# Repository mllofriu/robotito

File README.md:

# robotito
Robotito software and designs

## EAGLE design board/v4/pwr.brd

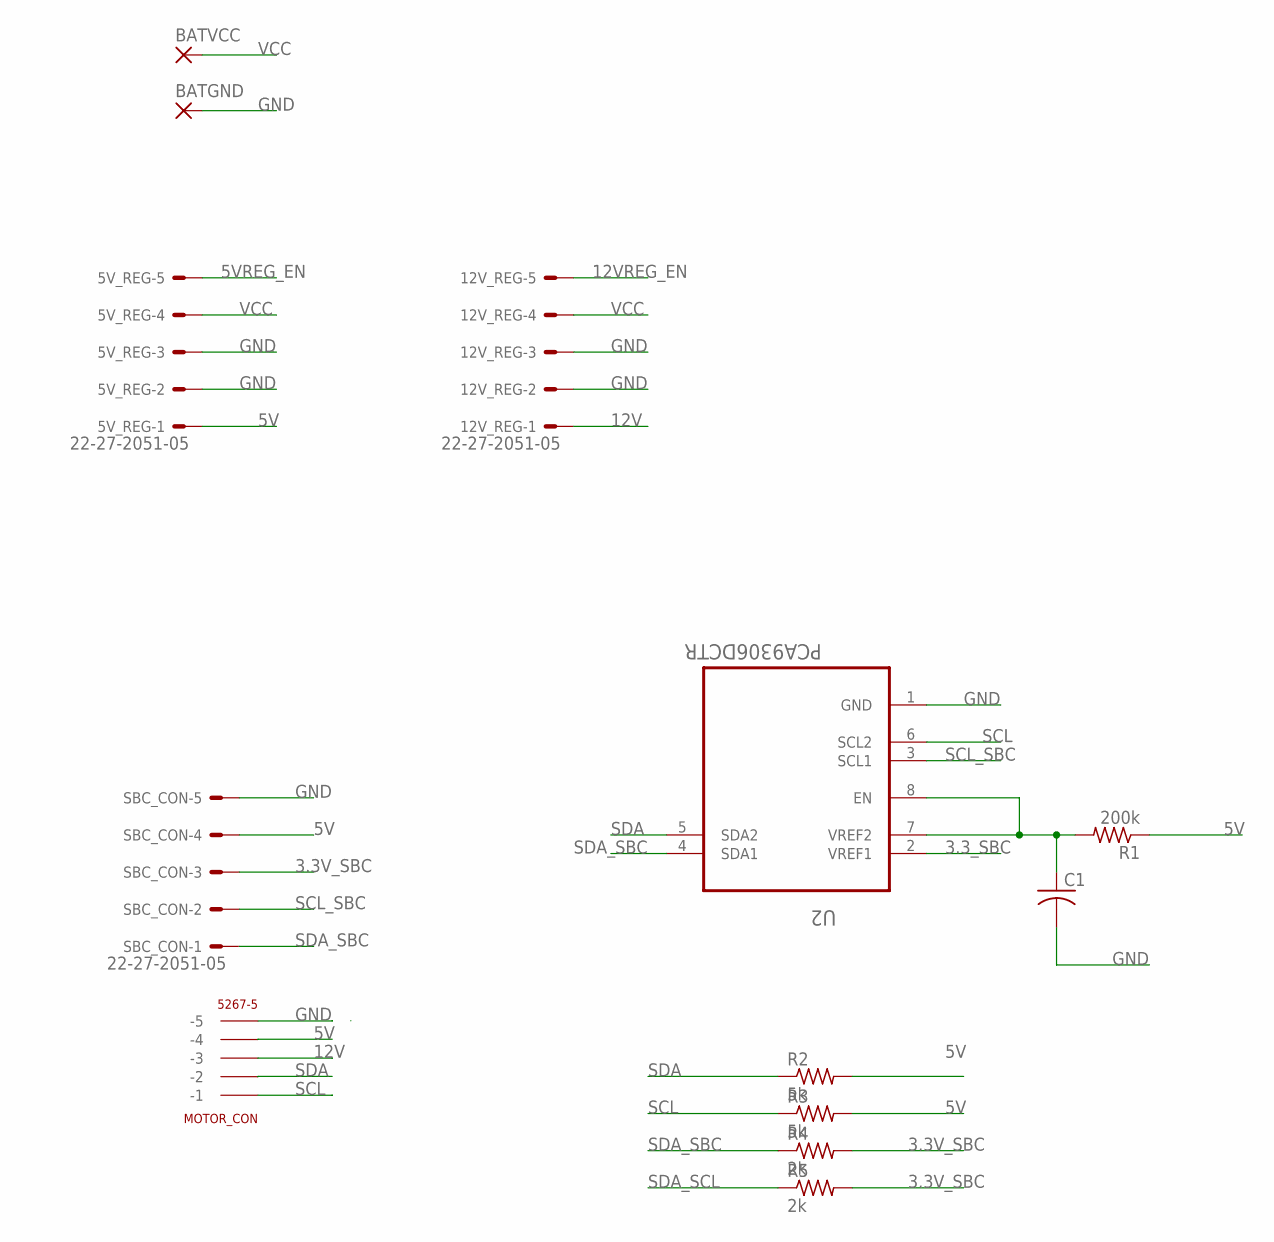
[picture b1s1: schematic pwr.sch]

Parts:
5V_REG, 12V_REG: 22-27-2051-05; 6410-05
BATGND: SMD5; SMD2,54-5,08
BATVCC: SMD5; SMD2,54-5,08
C1: C-USC1210; C1210
MOTOR_CON: 5267-5
R1: 200k; R1210
R2, R3: 5k; R1210
R4, R5: 2k; R1210
SBC_CON: 22-27-2051-05; 6410-05
U2: PCA9306DCTR; SOP65P400X130-8N

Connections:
3.3V_SBC: R4.2, R5.2, SBC_CON.3
3.3_SBC: U2.2 (VREF1)
5V: 5V_REG.1, MOTOR_CON.P$4 (-4), R1.1, R2.2, R3.2, SBC_CON.4
5VREG_EN: 5V_REG.5
12V: 12V_REG.1, MOTOR_CON.P$3 (-3)
12VREG_EN: 12V_REG.5
GND: 5V_REG.2, 5V_REG.3, 12V_REG.2, 12V_REG.3, BATGND.1, C1.2, MOTOR_CON.P$5 (-5), SBC_CON.5, U2.1 (GND)
unnamed: C1.1, R1.2, U2.7 (VREF2), U2.8 (EN)
SCL: MOTOR_CON.P$1 (-1), R3.1, U2.6 (SCL2)
SCL_SBC: SBC_CON.2, U2.3 (SCL1)
SDA: MOTOR_CON.P$2 (-2), R2.1, U2.5 (SDA2)
SDA_SBC: R4.1, SBC_CON.1, U2.4 (SDA1)
SDA_SCL: R5.1
VCC: 5V_REG.4, 12V_REG.4, BATVCC.1

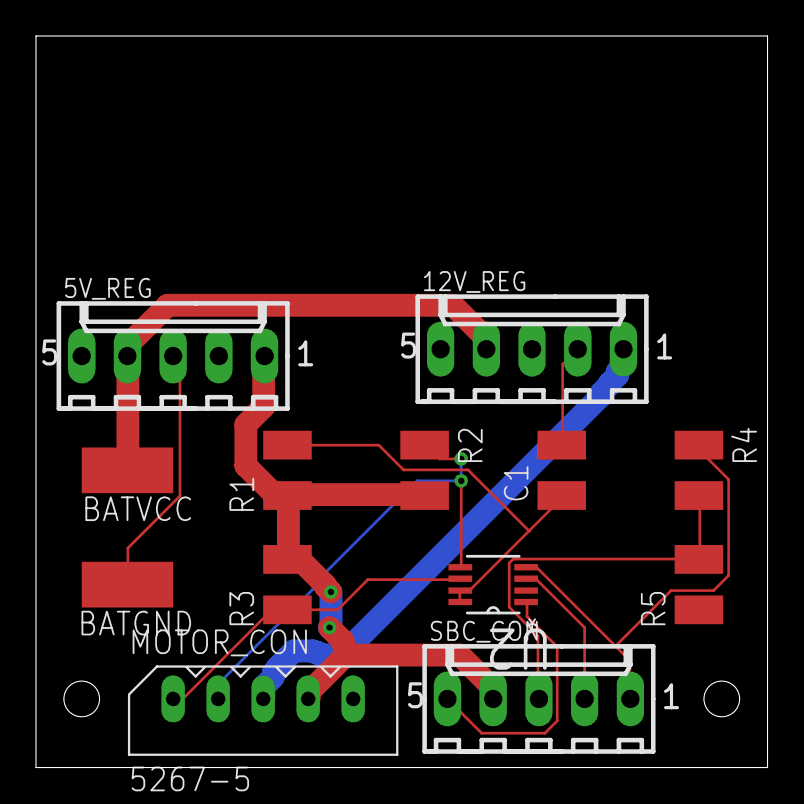
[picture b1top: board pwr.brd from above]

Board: 2 copper layers, 40.6 x 40.6 mm, 13 parts (0 on the bottom side), 10 nets.

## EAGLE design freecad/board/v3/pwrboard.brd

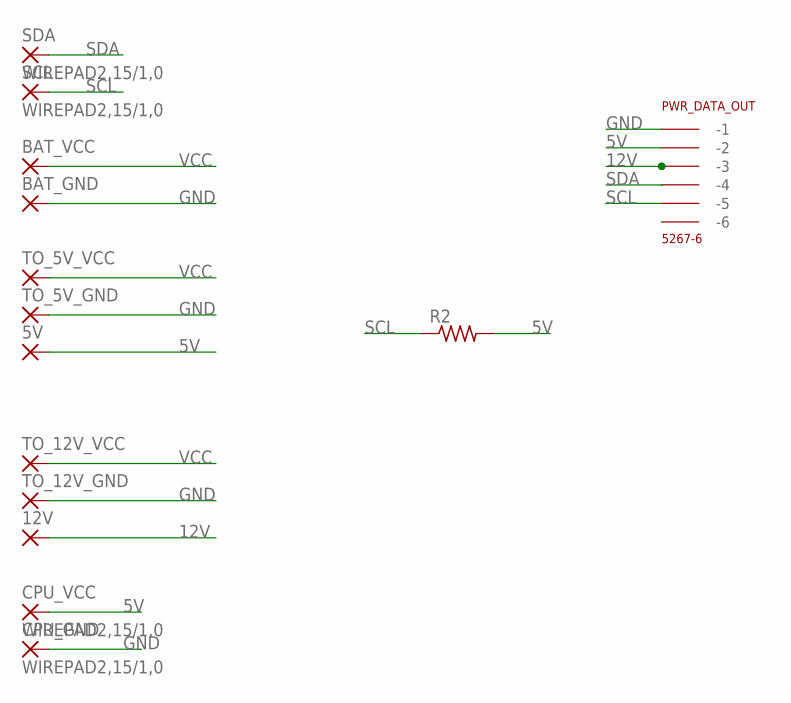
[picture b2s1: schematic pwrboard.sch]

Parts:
5V, 12V: SMD5; SMD2,54-5,08
BAT_GND: SMD5; SMD2,54-5,08
BAT_VCC: SMD5; SMD2,54-5,08
CPU_GND: WIREPAD2,15/1,0; 2,15/1,0
CPU_VCC: WIREPAD2,15/1,0; 2,15/1,0
PWR_DATA_OUT: 5267-6
R2: R-US_R1210; R1210
SCL: WIREPAD2,15/1,0; 2,15/1,0
SDA: WIREPAD2,15/1,0; 2,15/1,0
TO_5V_GND, TO_5V_VCC, TO_12V_GND, TO_12V_VCC: SMD5; SMD2,54-5,08

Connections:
5V: 5V.1, CPU_VCC.1, PWR_DATA_OUT.P$2 (-2), R2.2
12V: 12V.1, PWR_DATA_OUT.P$3 (-3)
GND: BAT_GND.1, CPU_GND.1, PWR_DATA_OUT.P$1 (-1), TO_5V_GND.1, TO_12V_GND.1
SCL: PWR_DATA_OUT.P$5 (-5), R2.1, SCL.1
SDA: PWR_DATA_OUT.P$4 (-4), SDA.1
VCC: BAT_VCC.1, TO_5V_VCC.1, TO_12V_VCC.1

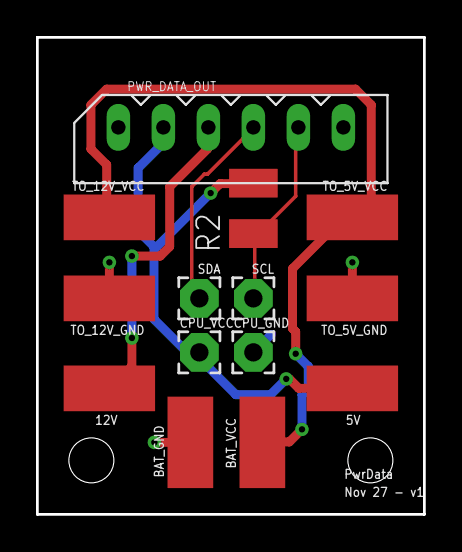
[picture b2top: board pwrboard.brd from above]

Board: 2 copper layers, 21.5 x 26.5 mm, 14 parts (0 on the bottom side), 6 nets.

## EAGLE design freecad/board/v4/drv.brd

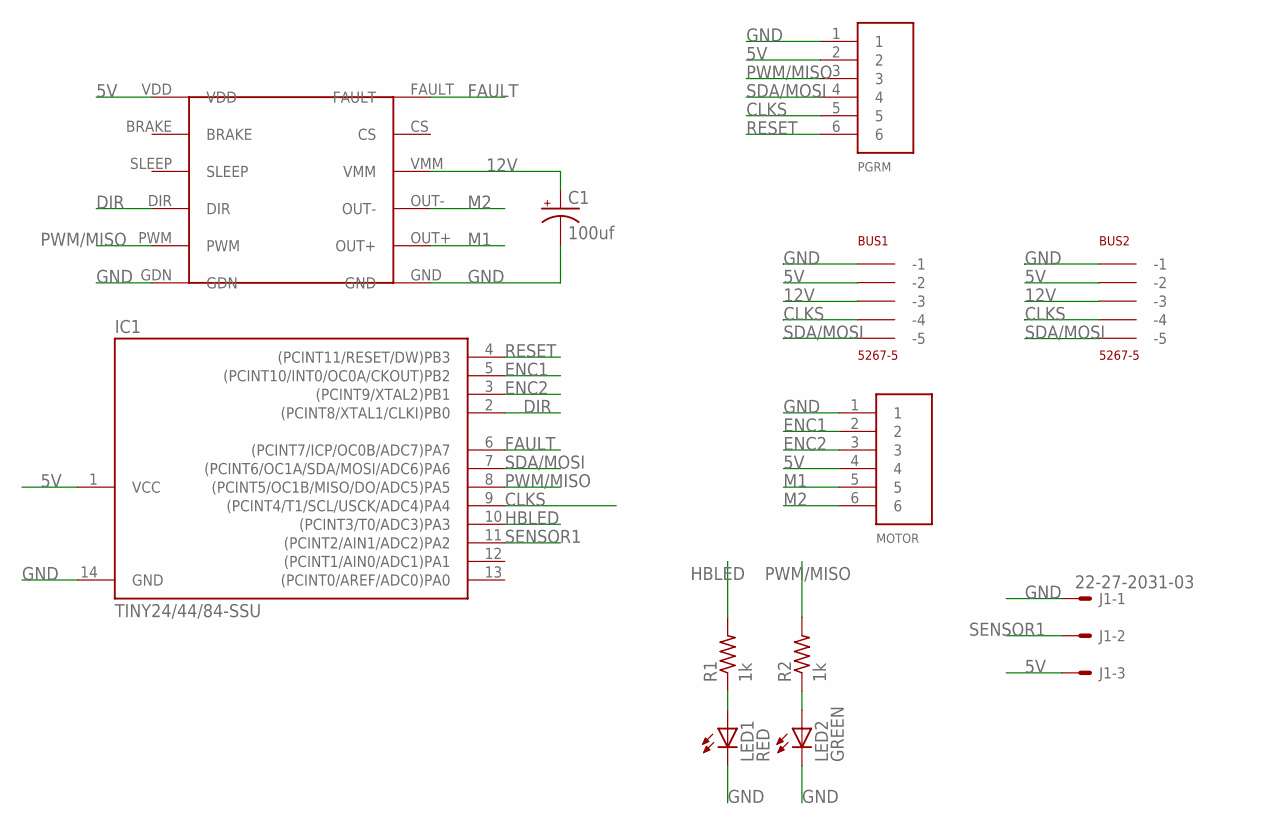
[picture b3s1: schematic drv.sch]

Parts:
BUS1, BUS2: 5267-5
C1: 100uf; E5-10,5
IC1: TINY24/44/84-SSU; SOIC14
J1: 22-27-2031-03; 6410-03
LED1: RED; 1206
LED2: GREEN; 1206
MOTOR: 6PIN; B6B-PH-K-S
PGRM: 6PIN; B6B-PH-K-S
R1, R2: 1k; M1206
U$1: DRV8801BR

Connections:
5V: BUS1.P$2 (-2), BUS2.P$2 (-2), IC1.1 (VCC), J1.3, MOTOR.4, PGRM.2, U$1.VDD
12V: BUS1.P$3 (-3), BUS2.P$3 (-3), C1.+, U$1.VMM
CLKS: BUS1.P$4 (-4), BUS2.P$4 (-4), IC1.9 ((PCINT4/T1/SCL/USCK/ADC4)PA4), PGRM.5
DIR: IC1.2 ((PCINT8/XTAL1/CLKI)PB0), U$1.DIR
ENC1: IC1.5 ((PCINT10/INT0/OC0A/CKOUT)PB2), MOTOR.2
ENC2: IC1.3 ((PCINT9/XTAL2)PB1), MOTOR.3
FAULT: IC1.6 ((PCINT7/ICP/OC0B/ADC7)PA7), U$1.FAULT
GND: BUS1.P$1 (-1), BUS2.P$1 (-1), C1.-, IC1.14 (GND), J1.1, LED1.C, LED2.C, MOTOR.1, PGRM.1, U$1.GDN, U$1.GND
HBLED: IC1.10 ((PCINT3/T0/ADC3)PA3), R1.2
M1: MOTOR.5, U$1.OUT+
M2: MOTOR.6, U$1.OUT-
unnamed: LED1.A, R1.1
unnamed: LED2.A, R2.1
PWM/MISO: IC1.8 ((PCINT5/OC1B/MISO/DO/ADC5)PA5), PGRM.3, R2.2, U$1.PWM
RESET: IC1.4 ((PCINT11/RESET/DW)PB3), PGRM.6
SDA/MOSI: BUS1.P$5 (-5), BUS2.P$5 (-5), IC1.7 ((PCINT6/OC1A/SDA/MOSI/ADC6)PA6), PGRM.4
SENSOR1: IC1.11 ((PCINT2/AIN1/ADC2)PA2), J1.2

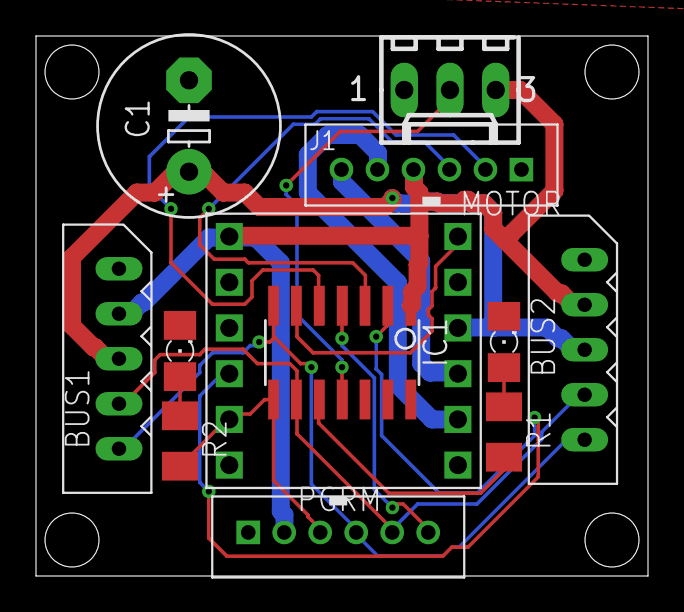
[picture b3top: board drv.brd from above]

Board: 2 copper layers, 34.0 x 30.0 mm, 12 parts (0 on the bottom side), 17 nets.

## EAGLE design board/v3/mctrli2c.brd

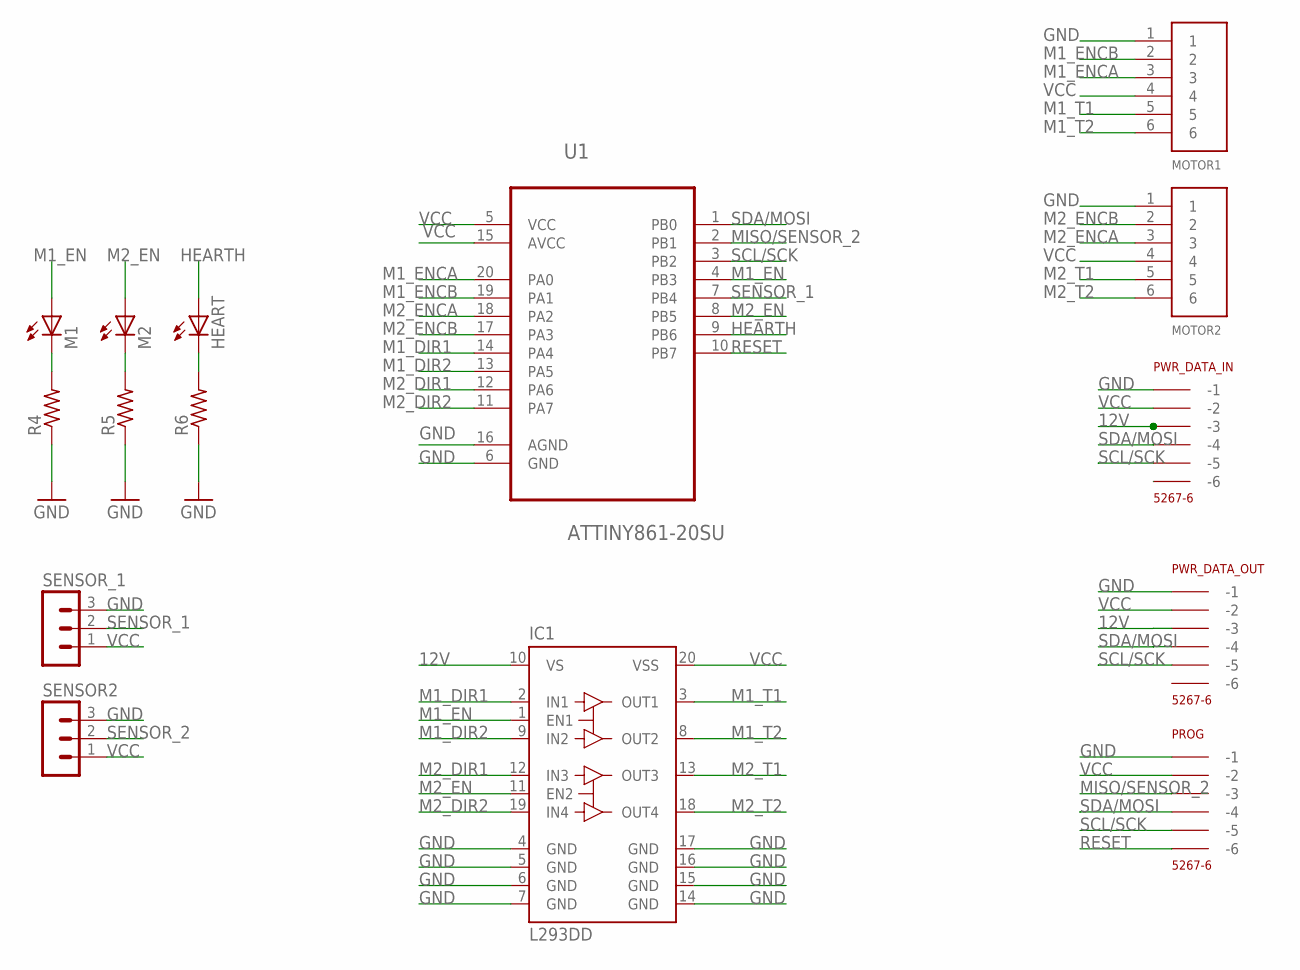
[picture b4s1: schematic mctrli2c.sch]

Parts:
HEART: LEDSML1206; SML1206
IC1: L293DD; SO20
M1, M2: LEDSML1206; SML1206
MOTOR1, MOTOR2: 6PIN; B6B-PH-K-S
PROG: 5267-6
PWR_DATA_IN: 5267-6
PWR_DATA_OUT: 5267-6
R4, R5, R6: R-US_R1210; R1210
SENSOR2: MA03-1
SENSOR_1: MA03-1
U1: ATTINY861-20SU; SOIC127P1032X265-20N

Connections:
12V: IC1.10 (VS), PWR_DATA_IN.P$3 (-3), PWR_DATA_OUT.P$3 (-3)
GND: IC1.4 (GND), IC1.5 (GND), IC1.6 (GND), IC1.7 (GND), IC1.14 (GND), IC1.15 (GND), IC1.16 (GND), IC1.17 (GND), MOTOR1.1, MOTOR2.1, PROG.P$1 (-1), PWR_DATA_IN.P$1 (-1), PWR_DATA_OUT.P$1 (-1), R4.1, R5.1, R6.1, SENSOR2.3, SENSOR_1.3, U1.6 (GND), U1.16 (AGND)
HEARTH: HEART.A, U1.9 (PB6)
M1_DIR1: IC1.2 (IN1), U1.14 (PA4)
M1_DIR2: IC1.9 (IN2), U1.13 (PA5)
M1_EN: IC1.1 (EN1), M1.A, U1.4 (PB3)
M1_ENCA: MOTOR1.3, U1.20 (PA0)
M1_ENCB: MOTOR1.2, U1.19 (PA1)
M1_T1: IC1.3 (OUT1), MOTOR1.5
M1_T2: IC1.8 (OUT2), MOTOR1.6
M2_DIR1: IC1.12 (IN3), U1.12 (PA6)
M2_DIR2: IC1.19 (IN4), U1.11 (PA7)
M2_EN: IC1.11 (EN2), M2.A, U1.8 (PB5)
M2_ENCA: MOTOR2.3, U1.18 (PA2)
M2_ENCB: MOTOR2.2, U1.17 (PA3)
M2_T1: IC1.13 (OUT3), MOTOR2.5
M2_T2: IC1.18 (OUT4), MOTOR2.6
MISO/SENSOR_2: PROG.P$3 (-3), U1.2 (PB1)
unnamed: M1.C, R4.2
unnamed: M2.C, R5.2
unnamed: HEART.C, R6.2
RESET: PROG.P$6 (-6), U1.10 (PB7)
SCL/SCK: PROG.P$5 (-5), PWR_DATA_IN.P$5 (-5), PWR_DATA_OUT.P$5 (-5), U1.3 (PB2)
SDA/MOSI: PROG.P$4 (-4), PWR_DATA_IN.P$4 (-4), PWR_DATA_OUT.P$4 (-4), U1.1 (PB0)
SENSOR_1: SENSOR_1.2, U1.7 (PB4)
SENSOR_2: SENSOR2.2
VCC: IC1.20 (VSS), MOTOR1.4, MOTOR2.4, PROG.P$2 (-2), PWR_DATA_IN.P$2 (-2), PWR_DATA_OUT.P$2 (-2), SENSOR2.1, SENSOR_1.1, U1.5 (VCC), U1.15 (AVCC)

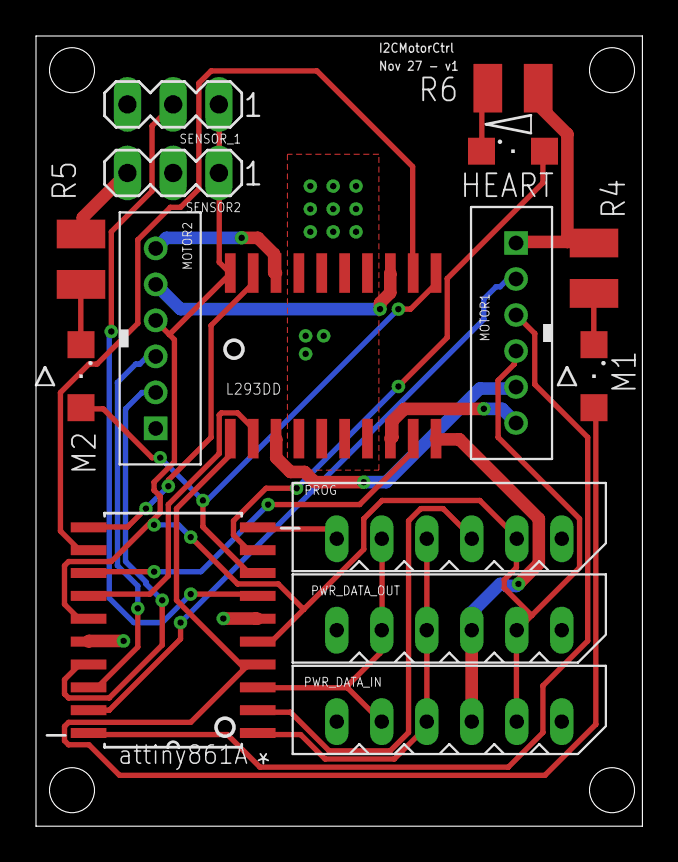
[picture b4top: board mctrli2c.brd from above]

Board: 2 copper layers, 33.7 x 43.9 mm, 15 parts (0 on the bottom side), 26 nets.

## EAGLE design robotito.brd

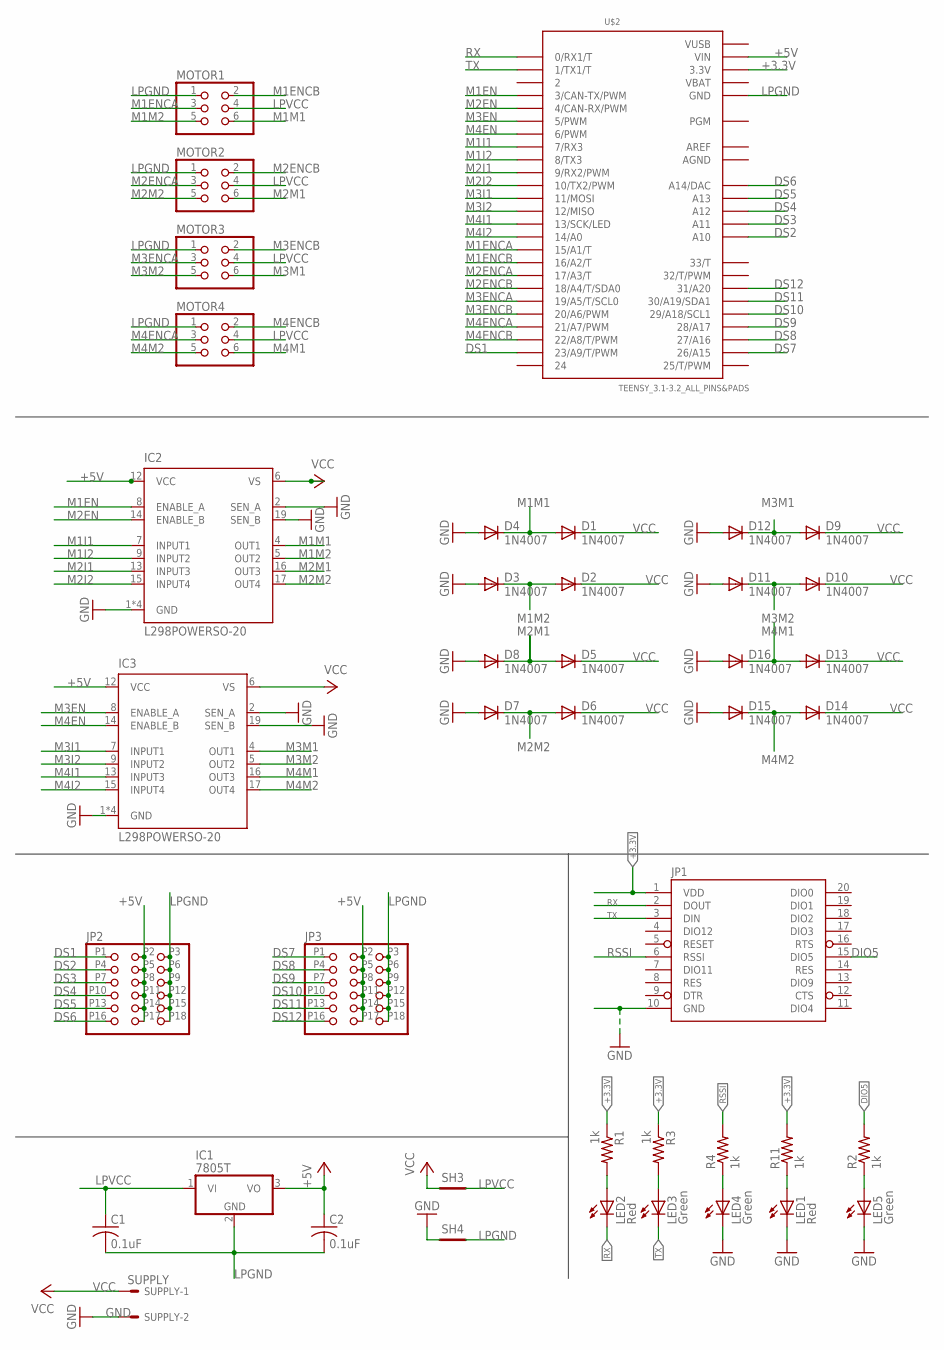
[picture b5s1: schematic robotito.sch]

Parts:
C1, C2: 0.1uF; C0805
D1, D2, D3, D4, D5, D6, D7, D8, D9, D10, D11, D12, D13, D14, D15, D16: 1N4007; DO41-10
IC1: 7805T; TO220H
IC2, IC3: L298POWERSO-20; POWERSO-20
JP1: XBEE-1B1; XBEE-1
JP2, JP3: PINHD-2X6; 2X06
LED1, LED2: Red; LED-0603
LED3, LED4, LED5: Green; LED-0603
MOTOR1, MOTOR2, MOTOR3, MOTOR4: PINHD-2X3; 2X03
R1, R2, R3, R4, R11: 1k; 0603-RES
SH3, SH4: SHORT-HT5; SHORT_TOP-50
SUPPLY: SUPPLY; 6410-02
U$2: TEENSY_3.1-3.2_ALL_PINS&PADS; TEENSY_3.0-3.2_ALL_PINS_&_PADS

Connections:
+3.3V: JP1.1 (VDD), R1.1, R3.1, R11.2, U$2.3.3V, U$2.3.3V1 (3.3V), U$2.3.3V2 (3.3V)
+5V: C2.1, IC1.3 (VO), IC2.12 (VCC), IC3.12 (VCC), JP2.P2, JP2.P5, JP2.P8, JP2.P11, JP2.P14, JP2.P17, JP3.P2, JP3.P5, JP3.P8, JP3.P11, JP3.P14, JP3.P17, U$2.VIN
AGND: U$2.AGND
AREF: U$2.AREF
DIO5: JP1.15 (DIO5), R2.2
DS1: JP2.P1, U$2.23/A9 (23/A9/T/PWM)
DS2: JP2.P4, U$2.A10
DS3: JP2.P7, U$2.A11
DS4: JP2.P10, U$2.A12
DS5: JP2.P13, U$2.A13
DS6: JP2.P16, U$2.RESET/DAC (A14/DAC)
DS7: JP3.P1, U$2.26 (26/A15)
DS8: JP3.P4, U$2.27 (27/A16)
DS9: JP3.P7, U$2.28 (28/A17)
DS10: JP3.P10, U$2.29 (29/A18/SCL1)
DS11: JP3.P13, U$2.30 (30/A19/SDA1)
DS12: JP3.P16, U$2.31 (31/A20)
GND: D3.A, D4.A, D7.A, D8.A, D11.A, D12.A, D15.A, D16.A, IC2.1 (GND), IC2.2 (SEN_A), IC2.10 (GND), IC2.11 (GND), IC2.19 (SEN_B), IC2.20 (GND), IC3.1 (GND), IC3.2 (SEN_A), IC3.10 (GND), IC3.11 (GND), IC3.19 (SEN_B), IC3.20 (GND), JP1.10 (GND), LED1.C, LED4.C, LED5.C, SH4.1, SUPPLY.2
LPGND: C1.2, C2.2, IC1.2 (GND), JP2.P3, JP2.P6, JP2.P9, JP2.P12, JP2.P15, JP2.P18, JP3.P3, JP3.P6, JP3.P9, JP3.P12, JP3.P15, JP3.P18, MOTOR1.1, MOTOR2.1, MOTOR3.1, MOTOR4.1, SH4.2, U$2.GND, U$2.GND1 (GND), U$2.GND2 (GND)
LPVCC: C1.1, IC1.1 (VI), MOTOR1.4, MOTOR2.4, MOTOR3.4, MOTOR4.4, SH3.2
M1EN: IC2.8 (ENABLE_A), U$2.3 (3/CAN-TX/PWM)
M1ENCA: MOTOR1.3, U$2.15/A1 (15/A1/T)
M1ENCB: MOTOR1.2, U$2.16/A2 (16/A2/T)
M1I1: IC2.7 (INPUT1), U$2.7 (7/RX3)
M1I2: IC2.9 (INPUT2), U$2.8 (8/TX3)
M1M1: D1.A, D4.C, IC2.4 (OUT1), MOTOR1.6
M1M2: D2.A, D3.C, IC2.5 (OUT2), MOTOR1.5
M2EN: IC2.14 (ENABLE_B), U$2.4 (4/CAN-RX/PWM)
M2ENCA: MOTOR2.3, U$2.17/A3 (17/A3/T)
M2ENCB: MOTOR2.2, U$2.18/A4 (18/A4/T/SDA0)
M2I1: IC2.13 (INPUT3), U$2.9 (9/RX2/PWM)
M2I2: IC2.15 (INPUT4), U$2.10 (10/TX2/PWM)
M2M1: D5.A, D8.C, IC2.16 (OUT3), MOTOR2.6
M2M2: D6.A, D7.C, IC2.17 (OUT4), MOTOR2.5
M3EN: IC3.8 (ENABLE_A), U$2.5 (5/PWM)
M3ENCA: MOTOR3.3, U$2.19/A5 (19/A5/T/SCL0)
M3ENCB: MOTOR3.2, U$2.20/A6 (20/A6/PWM)
M3I1: IC3.7 (INPUT1), U$2.11 (11/MOSI)
M3I2: IC3.9 (INPUT2), U$2.12 (12/MISO)
M3M1: D9.A, D12.C, IC3.4 (OUT1), MOTOR3.6
M3M2: D10.A, D11.C, IC3.5 (OUT2), MOTOR3.5
M4EN: IC3.14 (ENABLE_B), U$2.6 (6/PWM)
M4ENCA: MOTOR4.3, U$2.21/A7 (21/A7/PWM)
M4ENCB: MOTOR4.2, U$2.22/A8 (22/A8/T/PWM)
M4I1: IC3.13 (INPUT3), U$2.13 (13/SCK/LED)
M4I2: IC3.15 (INPUT4), U$2.14/A0
M4M1: D13.A, D16.C, IC3.16 (OUT3), MOTOR4.6
M4M2: D14.A, D15.C, IC3.17 (OUT4), MOTOR4.5
unnamed: LED1.A, R11.1
unnamed: LED2.A, R1.2
unnamed: LED3.A, R3.2
unnamed: LED4.A, R4.1
unnamed: LED5.A, R2.1
RSSI: JP1.6 (RSSI), R4.2
RX: JP1.2 (DOUT), LED2.C, U$2.0 (0/RX1/T)
TX: JP1.3 (DIN), LED3.C, U$2.1 (1/TX1/T)
VBAT: U$2.VBAT
VCC: D1.C, D2.C, D5.C, D6.C, D9.C, D10.C, D13.C, D14.C, IC2.6 (VS), IC3.6 (VS), SH3.1, SUPPLY.1
VUSB: U$2.VUSB

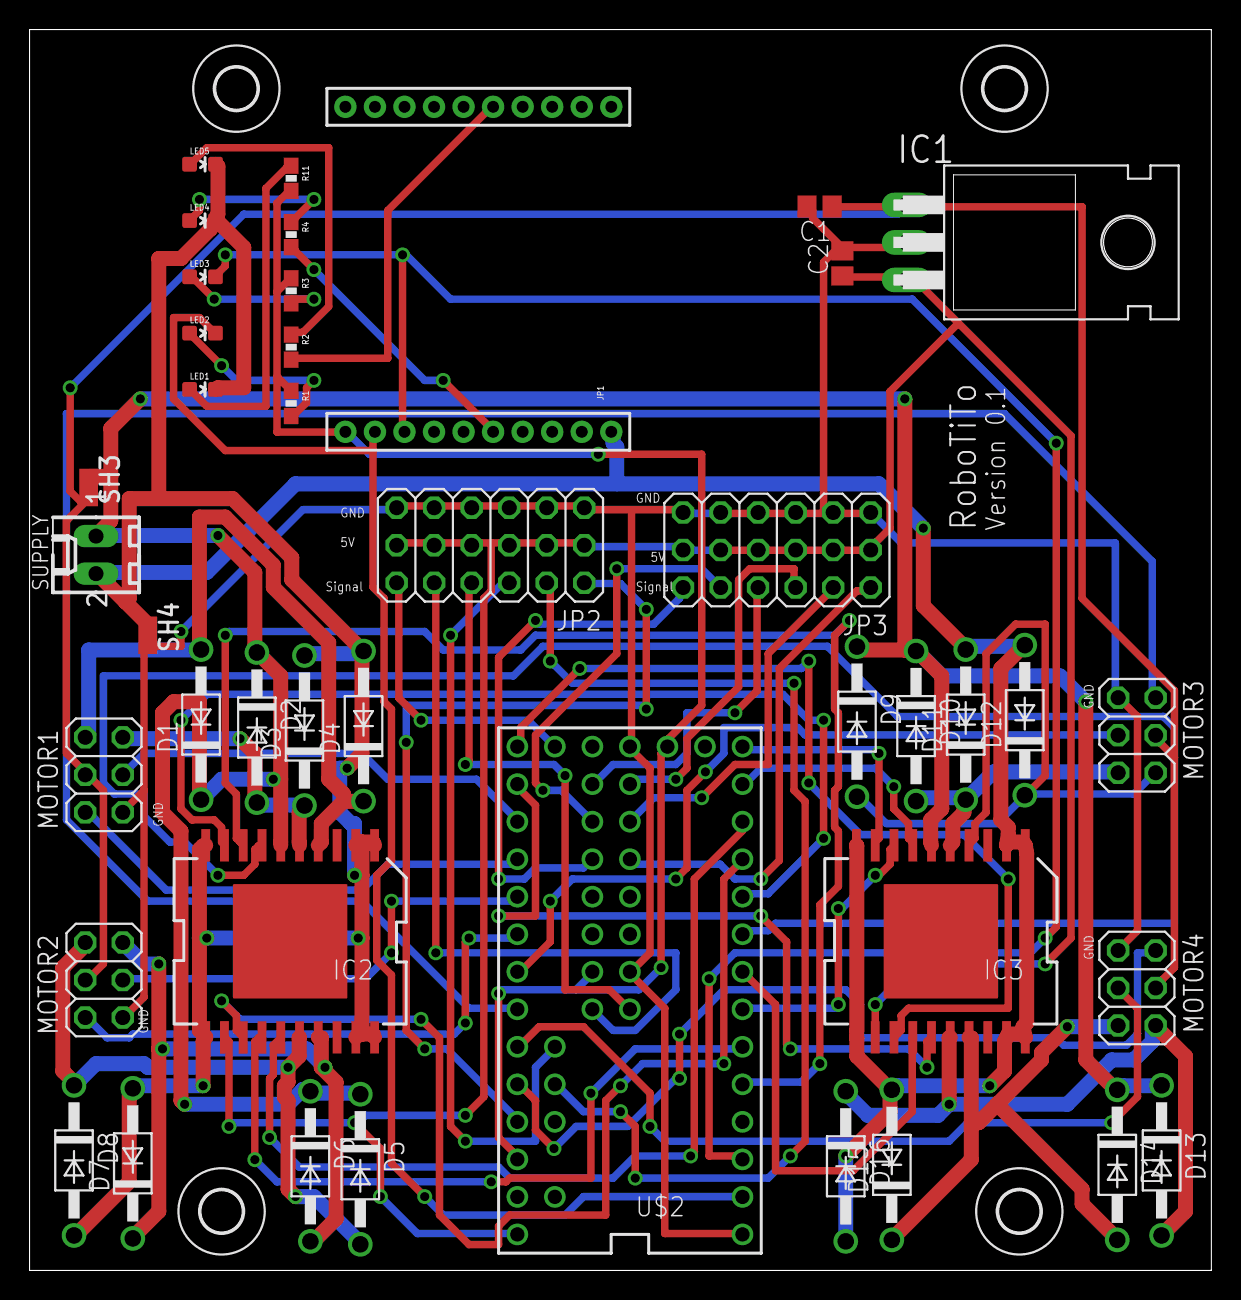
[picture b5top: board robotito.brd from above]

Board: 2 copper layers, 80.0 x 84.0 mm, 46 parts (0 on the bottom side), 55 nets.

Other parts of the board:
U$1, U$3, U$4, U$5: 2,8

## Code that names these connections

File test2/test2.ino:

int m1en = 3;
int m2en = 4;
int m3en = 5;
int m4en = 6;

int m1i1 = 7;
int m1i2 = 8;
int m2i1 = 9;
int m2i2 = 10;
int m3i1 = 11;
int m3i2 = 12;
int m4i1 = 13;
int m4i2 = 14;

int vel = 100;
int restdelay = 1500;

void setup(){
  pinMode(m1en, OUTPUT);
  pinMode(m1i1, OUTPUT);
  pinMode(m1i2, OUTPUT);
  
  pinMode(m2en, OUTPUT);
  pinMode(m2i1, OUTPUT);
  pinMode(m2i2, OUTPUT);
  
  pinMode(m3en, OUTPUT);
  pinMode(m3i1, OUTPUT);
  pinMode(m3i2, OUTPUT);
  
  pinMode(m4en, OUTPUT);
  pinMode(m4i1, OUTPUT);
  pinMode(m4i2, OUTPUT);


  digitalWrite(m1i1, LOW);
  digitalWrite(m1i2, LOW);
  analogWrite(m1en, 0);
  
  digitalWrite(m2i1, LOW);
  digitalWrite(m2i2, LOW);
  analogWrite(m2en, 0);
  
  digitalWrite(m3i1, LOW);
  digitalWrite(m3i2, LOW);
  analogWrite(m3en, 0);
  
  digitalWrite(m4i1, LOW);
  digitalWrite(m4i2, LOW);
  analogWrite(m4en, 0);

 
}

void loop(){
  analogWrite(m1en, 0);
  analogWrite(m2en, 0);
  analogWrite(m3en, 0);
  analogWrite(m4en, 0);

  delay(restdelay);

  digitalWrite(m1i1, HIGH);
  digitalWrite(m1i2, LOW);
  digitalWrite(m3i1, LOW);
  digitalWrite(m3i2, HIGH);

  analogWrite(m1en, vel);
  analogWrite(m3en, vel);

  delay(restdelay);

  analogWrite(m1en, 0);
  analogWrite(m2en, 0);
  analogWrite(m3en, 0);
  analogWrite(m4en, 0);

  delay(restdelay);
  
  digitalWrite(m3i1, HIGH);
  digitalWrite(m3i2, LOW);
  digitalWrite(m1i1, LOW);
  digitalWrite(m1i2, HIGH);

  analogWrite(m1en, vel);
  analogWrite(m3en, vel);

  delay(restdelay);

}  

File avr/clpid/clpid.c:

#define F_CPU 8000000 // or whatever may be your frequency
 
#include <avr/io.h>
#include <util/delay.h>                // for _delay_ms()
#include <avr/interrupt.h>

#define M1_DIRA_P PORTA
#define M1_DIRA_N PA4
#define M1_DIRB_P PORTA
#define M1_DIRB_N PA5
#define M1_EN_P PORTB
#define M1_EN_N	PB3

#define M2_DIRA_P PORTA
#define M2_DIRA_N PA6
#define M2_DIRB_P PORTA
#define M2_DIRB_N PA7
#define M2_EN_P PORTB
#define M2_EN_N	PB5

#define INT_QUAD_A PCINT0
#define INT_QUAD_B PCINT1
#define PIN_QUAD PINA
#define PIN_QUAD_A PINA0
#define PIN_QUAD_B PINA1
#define PORT_QUAD_A PORTA0
#define PORT_QUAD_B PORTA1
#define DDR_QUAD DDRA

#define HB_DDR DDRB
#define HB_P PORTB
#define HB_N PORTB6

#define CONTROL_PERIOD_MS 100
#define CONTROL_PERIOD_S (.1)

#define DEFAULT_KP 20
#define DEFUALT_KTI .5

// The target tic counts for a control period 
static int16_t target;
// The tic counts for the current control period
static int16_t current;
// The proportional constant of the PI controller
static int16_t kp;
// The integral constant of the PI controller
static int16_t ki;
// Cached value of the target times the prop constant
static int16_t target_p;
// Cached value of the target times the integral constant
static int16_t target_i;
// Maximum allowed e * ki
static int16_t max_e_ki;
// The accumulated error times the prop constant
static int16_t pe;
// The accumulated error times the integral constant
static int16_t ie;
// The state of the encoder word
static uint8_t pin_quad, pin_quad_masked;


void set_target(int16_t tics_per_sec)
{
	int16_t tics_per_period = 
		tics_per_sec * CONTROL_PERIOD_S;
	target = tics_per_period;
	// TODO: overflow?
	target_p = target * kp;
	target_i = target * ki;
}

void setup_motors()
{
	DDRA = (1 << M1_DIRA_N) | (1 << M1_DIRB_N) | (1 << M2_DIRA_N) | (1 << M2_DIRB_N);
	DDRB |= 1 << M1_EN_N;
	DDRB |= 1 << M2_EN_N;

  TCCR1A = (1 << COM1B1) | (0 << COM1B0) | (1 << PWM1B);
	TCCR1C |= (1 << COM1D1) | (0 << COM1D0) | (1 << PWM1D);
	TCCR1B = (1 << CS10);
  TCCR1D = (0 << WGM11) | (0 << WGM10);
}


int main(void)
{
	// Set quad pins as input	
	DDR_QUAD &= ~(1 << PORT_QUAD_A);
	DDR_QUAD &= ~(1 << PORT_QUAD_B);
	//PORTA = 1 << PA2 | 1 << PA3;

	// Initialize variables
	target = 0;
	current = 0;
	pe = 0; ie = 0;
	target_p = 0; target_i = 0;
	max_e_ki = (int32_t) 256 * 128 - 1;
	pin_quad = PIN_QUAD;
	pin_quad_masked = pin_quad & 
		(1 << PIN_QUAD_A | 1 << PIN_QUAD_B);
	kp = DEFAULT_KP;
	ki = DEFUALT_KTI * DEFAULT_KP;
	// Enable the HearthBeat LED
	HB_DDR |= 1 << HB_N;
	
	int i;
	for (i = 0; i < 5; i++){
		HB_P |= 1 << HB_N;
		_delay_ms(100);
		HB_P &= ~(1 << HB_N);
		_delay_ms(100);
	}
	
	setup_motors();

	// TODO: Install interrupt to perform a control loop on timer


	// Set target to test
	int motor_red = 30;
	int gear_red = 1;
	int tics_per_turn = 12;
	int target_rps = 1;
	set_target(-motor_red * gear_red * tics_per_turn * target_rps);

	// Enable interrupt to handle encoder updates
	// Enable Interrupts for changes in pins PCINT[7:0] or PCINT[15:12]	
	GIMSK |= (1<<PCIE1);	
	// Enable the individual ports
	PCMSK0 = 0;
	PCMSK1 = 0;
	PCMSK0 |= (1<<INT_QUAD_A);
	PCMSK0 |= (1<<INT_QUAD_B);
	sei();

	M1_DIRA_P &= ~(1 << M1_DIRA_N);
	M1_DIRB_P |= (1 << M1_DIRB_N);
	//OCR1B = 150; 
	int iter = 0;
	while (1){
		
		// Use the last 8 bits for pwm - last bit is used for sign
		// TODO: overflow?
		int16_t pwm = pe / 128 + ie / 128;
		if (pwm < 0) {
			M1_DIRA_P &= ~(1 << M1_DIRA_N);
			M1_DIRB_P |= (1 << M1_DIRB_N);
			pwm = -pwm;
		} else {
			M1_DIRA_P |= (1 << M1_DIRA_N);
			M1_DIRB_P &= ~(1 << M1_DIRB_N);
		}
		OCR1B = pwm;
		// Reset pe to target * kp as the error is now target
		pe = target_p;
		// Add target * ki to the accumulated error * ki = ie
		// Watch for max_e_ki
		if (target_i > 0) {
			if (ie < max_e_ki - target_i)
				ie += target_i;
			else 
				ie = max_e_ki;
		} else if (target_i < 0) {
			if (ie > -max_e_ki - target_i)
				ie += target_i;
			else 
				ie = -max_e_ki;
		} 
		// Reset the current count of tics
		current = 0;
	
		iter ++;
		if (iter % 20 == 0) {
			target_rps = (target_rps + 1) % 8;
			set_target(-motor_red * gear_red * tics_per_turn * target_rps); 
		}

		_delay_ms(CONTROL_PERIOD_MS);
	}

}

int count=0;
// Interrupt routine for changes in pins 8:11
ISR(PCINT_vect){

	// http://www.me.unm.edu/~starr/teaching/me470/quad.pdf
	// Read new state
	uint8_t new_pin_quad = PIN_QUAD;

	uint8_t new_pin_quad_masked = new_pin_quad & 
		(1 << PIN_QUAD_A | 1 << PIN_QUAD_B);
	// Other unrelated pins might be triggering the interrupt
	// only perform computations if one of the pins is involved
	if (pin_quad_masked != new_pin_quad_masked) {
		// b_old ^ a_new == 1 iff dir is pos
		uint8_t b_old = pin_quad >> PIN_QUAD_B;
		uint8_t a_new = new_pin_quad >> PIN_QUAD_A;
		uint8_t dir = (a_new ^ b_old) & 1;
	
		if ((current < target && dir) || 
				(current > target && !dir)){
			pe -= kp;
			if (ie > -max_e_ki + ki)
				ie -= ki;
			else
				ie = -max_e_ki;
		} else if ((current >= target && dir) || 
				(current <= target && !dir)){
			pe += kp;
			if (ie < max_e_ki - ki)
				ie += ki;
			else
				ie = max_e_ki;
		}

		
		if (dir) {
			current++;
		} else {
			current--;
		}

		// Save new state as old
		pin_quad = new_pin_quad;
		pin_quad_masked = new_pin_quad_masked;

		count++;
		if (count % 100	 == 0)
			HB_P ^= 1 << HB_N;
	}

	
}

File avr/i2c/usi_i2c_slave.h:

	/*-----------------------------------------------------*\
|  USI I2C Slave Driver                                 |
|                                                       |
| This library provides a robust, interrupt-driven I2C  |
| slave implementation built on the ATTiny Universal    |
| Serial Interface (USI) hardware.  Slave operation is  |
| implemented as a register bank, where each 'register' |
| is a pointer to an 8-bit variable in the main code.   |
| This was chosen to make I2C integration transparent   |
| to the mainline code and making I2C reads simple.     |
| This library also works well with the Linux I2C-Tools |
| utilities i2cdetect, i2cget, i2cset, and i2cdump.     |
|                                                       |
| Adam Honse (GitHub: CalcProgrammer1) - 7/29/2012      |
|            -calcprogrammer1@gmail.com                 |
\*-----------------------------------------------------*/
#ifndef USI_I2C_SLAVE_H
#define USI_I2C_SLAVE_H

#include <avr/io.h>
#include <avr/interrupt.h>

//Microcontroller Dependent Definitions
#if defined (__AVR_ATtiny24__) | \
	defined (__AVR_ATtiny44__) | \
	defined (__AVR_ATtiny84__) | \
	defined (__AVR_ATtiny24A__)
	#define DDR_USI			DDRA
	#define PORT_USI		PORTA
	#define PIN_USI			PINA
	#define PORT_USI_SDA	PA6
	#define PORT_USI_SCL	PA4
	#define PIN_USI_SDA		PINA6
	#define PIN_USI_SCL		PINA4
#endif

#if defined(__AVR_AT90Tiny2313__) | \
	defined(__AVR_ATtiny2313__)
    #define DDR_USI             DDRB
    #define PORT_USI            PORTB
    #define PIN_USI             PINB
    #define PORT_USI_SDA        PB5
    #define PORT_USI_SCL        PB7
    #define PIN_USI_SDA         PINB5
    #define PIN_USI_SCL         PINB7
#endif

#if defined( __AVR_ATtiny261__ ) | \
     defined( __AVR_ATtiny461__ ) | \
     defined( __AVR_ATtiny861__ )
    #define DDR_USI             DDRB
    #define PORT_USI            PORTB
    #define PIN_USI             PINB
    #define PORT_USI_SDA        PB0
    #define PORT_USI_SCL        PB2
    #define PIN_USI_SDA         PINB0
    #define PIN_USI_SCL         PINB2
#endif

//USI I2C Initialize
//  address - If slave, this parameter is the slave address
void USI_I2C_Init(char address);

#endif

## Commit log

2015-11-27 functional self programmed pid
2015-11-27 Using PID library
2015-11-27 Using ff control
2015-11-30 FF model self calibration
2017-01-02 board development
2017-01-03 Board is routing good with ~100 vias
2017-01-03 fixed one motor connector, thinned wires
2017-01-03 fixed some errors/warnings
2017-01-05 juan and tj improvements draft
2017-01-05 switch to powerso and .1 inch for sensors
2017-01-05 added pads to board
2017-01-05 added holes and resized
2017-01-05 fix routing errors. v .1
2017-01-06 budget and print ready
2017-01-06 update budget
2017-01-10 Parts update
2017-01-11 Fix separation to comply with pcbway. V1 sent to print
2017-01-16 part list update
2017-02-04 some demoes
2017-02-06 improved tests. RobotitoDemo counts tics, spin demo for fast spin
2017-03-12 Added tests for sensor and xbee.
2017-03-14 robotito 4-wheels and xbee api mode
2017-03-14 xbee api mode test
2017-03-16 Refactor and make it a ros pkg
2017-03-16 Added xbee test program
2017-03-16 first draft of pilot node, saving last cmd_vel to send to robot
2017-03-16 forward backwards working, drifts, and there is a little lag to send
2017-03-16 delay fixed, faster consumption in robot, also no acks
2017-03-17 Fix wheels angles, now it's controllable. Setting vel to low for now
2017-03-31 added firmware to this project, receiving sonar info, but introduces delays
2017-03-31 moving firmware to arduino folder
2017-04-03 sending packets for sensors but keeping responsiveness
2017-04-03 Receive sonar msgs in pilot
2017-04-03 added urdf with one distance sensor
2017-04-03 publish range sensors and low to 20 hz control/sensor cycle
2017-04-03 Sensor holder part
2017-04-04 add sensor holder part
2017-04-04 Receive sensor media, plot in rviz
2017-04-04 Factor sensor reading and sensing in a class
2017-04-04 Motor manager
2017-04-04 Managers return control period to the main program
2017-07-11 pose detector launch
2017-07-11 pose detector publisher
2017-07-11 kicker
2017-07-11 fixes to pose publisher
2017-07-13 Tag holder and tags for print
2017-07-14 Add timeout to auto stop
2017-07-14 Corrected motion equations
2017-07-14 Fixed calibration and camera distances
2017-07-18 Release motors functionality
2017-07-18 Update PID constants
2017-07-18 fix to comply with new protocol
2017-07-18 kicker in freecad
2017-07-18 add release motors after timeout
2017-07-19 Increase timeout time. Blink at start to detect restarts.
2017-07-21 Reduce medians to decrease lag
2017-07-21 Freecad design of robotito
2017-07-24 Detect walls using markers 1-4 and publish as PoseStamped
2017-07-27 draft on using aruco
2017-07-28 tune control
2017-07-28 Tune detection system
2017-07-28 new designs in freecad
2017-08-01 fix sensorholder
2018-08-31 Second round of freecad design with assembly
2018-10-02 Motor module
2018-11-12 printed motor module
2018-11-13 printed motor module, stoppers and module synced
2018-12-02 Motor module working
2018-12-03 Big base and motor module adjustments
2018-12-03 Moved motor module files to own folder
2018-12-03 Motor module assembly
2018-12-04 Assembly for robot 15cm
2018-12-20 V2 boards plus some mods for v3
2018-12-22 first controller, not thouroughly tested
2018-12-22 Updates to the board and cad
2018-12-30 TinyWireS class interface working for i2cpid
2018-12-30 Request for data working
2018-12-30 Implemented motor controller as a class
2019-01-02 Kp seems ok, need ki for it to work
2019-01-02 Fix ki
2019-01-04 make controller independent of time, increase freq to 200 hz
2019-01-05 document controller
2019-01-05 Add macro to setup motor ports
2019-01-07 Change api to set_target as tics_per_period. Working i2c comm
2019-01-07 Fix bug in controller
2019-01-12 Send stuff through i2c. Enable/disable api
2019-01-12 Remove files from git
2019-01-13 First version of 8801 and at24
2019-01-16 Back to old compiler flags
2019-01-16 remove unneded variables
2019-01-16 Update usi start vect name
2019-01-16 Use shift for scale factor, receive constants already multiplied by control period
2019-01-16 Define names for start vector (fix)
2019-01-16 Reduce buffer sizes
2019-01-16 target init const expr
2019-01-16 Add fuses to makefile
2019-01-16 Simplify protocol
2019-05-07 motor module tuneup
2019-05-07 One motor controller
2019-06-08 Controller working with 8801 and custom board.
    Executing make fuses is imperative
2019-06-08 Restore the 9 byte protocol
2019-06-20 Motor module with controller mounts
2020-04-25 Change computers
2020-04-25 8801 motor controller board

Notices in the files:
parts and their libraries:
SparkFun-RF: Licensing: Creative Commons ShareAlike 4.0 International - https://creativecommons.org/licenses/by-sa/4.0
